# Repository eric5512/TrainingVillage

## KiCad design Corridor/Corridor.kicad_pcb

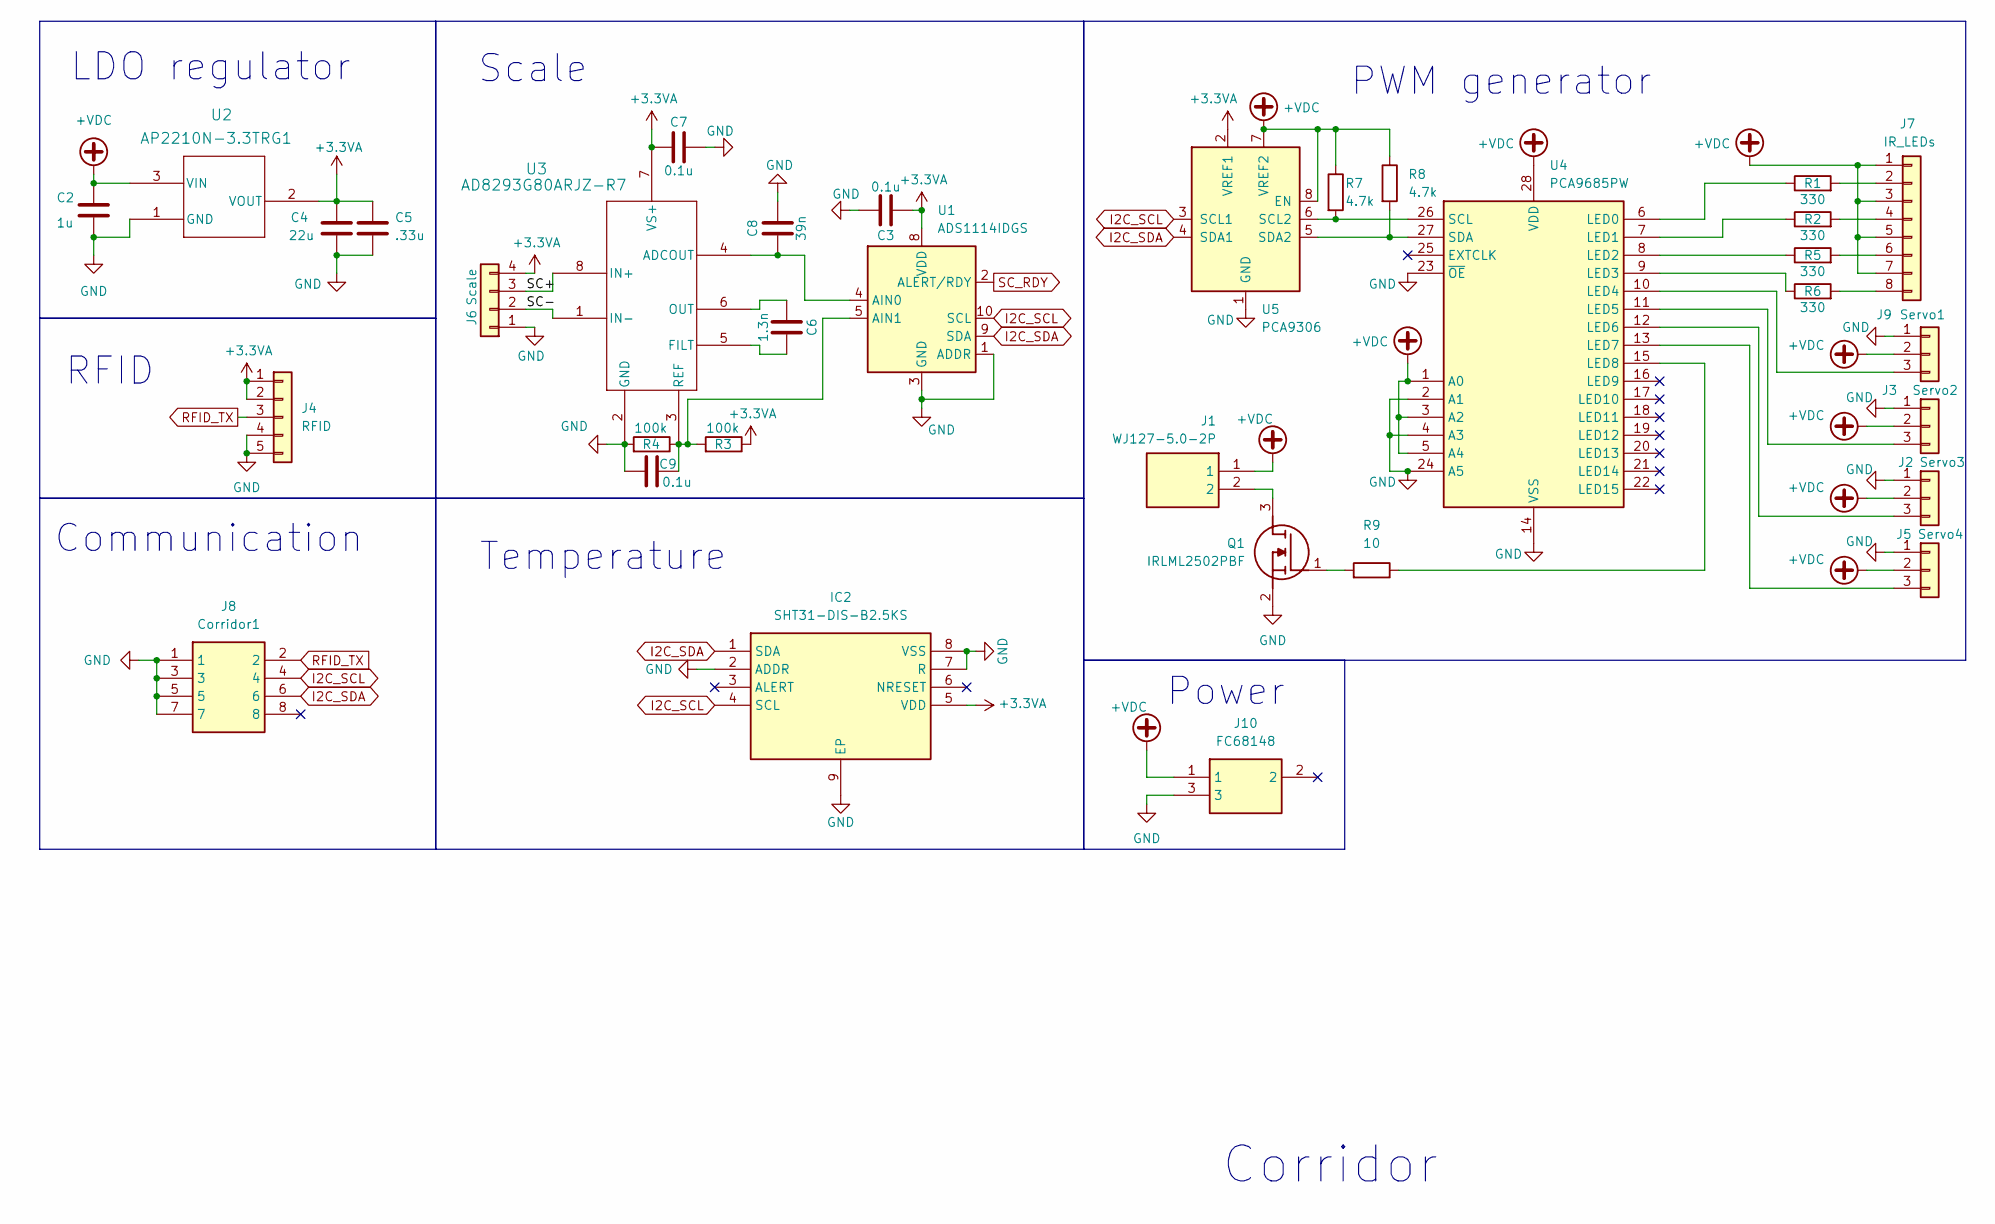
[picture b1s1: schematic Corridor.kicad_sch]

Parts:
C2: 1u; C_1206_3216Metric_Pad1.33x1.80mm_HandSolder
C3, C7, C9: 0.1u; C_1206_3216Metric_Pad1.33x1.80mm_HandSolder
C4: 22u; C_Elec_5x5.8
C5: .33u; C_1206_3216Metric_Pad1.33x1.80mm_HandSolder
C6: 1.3n; C_1206_3216Metric_Pad1.33x1.80mm_HandSolder
C8: 39n; C_1206_3216Metric_Pad1.33x1.80mm_HandSolder
IC2: SHT31-DIS-B2.5KS; SON50P250X250X100-9N-D; Manufacturer_Part_Number SHT31-DIS-B2.5KS; Mouser Part Number 403-SHT31-DIS-B
J1: WJ127-5.0-2P; WJ127502P; Manufacturer_Part_Number WJ127-5.0-2P
J2: Servo3; PinHeader_1x03_P2.54mm_Vertical
J3: Servo2; PinHeader_1x03_P2.54mm_Vertical
J4: RFID; JST_PH_B5B-PH-K_1x05_P2.00mm_Vertical
J5: Servo4; PinHeader_1x03_P2.54mm_Vertical
J6: Scale; JL308-25404G01
J7: IR_LEDs; JL500_8
J8: Corridor1; RJ45R08P-A004; Manufacturer_Part_Number RJ45R08P-A004
J9: Servo1; PinHeader_1x03_P2.54mm_Vertical
J10: FC68148; Manufacturer_Part_Number FC68148
Q1: IRLML2502PBF; SOT95P237X112-3N; Manufacturer_Part_Number IRLML2502PBF; Mouser Part Number N/A
R1, R2, R5, R6: 330; R_1206_3216Metric
R3, R4: 100k; R_1206_3216Metric_Pad1.30x1.75mm_HandSolder
R7, R8: 4.7k; R_0805_2012Metric
R9: 10; R_1206_3216Metric
U1: ADS1114IDGS; DGS10
U2: AP2210N-3.3TRG1; SOT_3.3TRG1_DIO
U3: AD8293G80ARJZ-R7; RJ_8_ADI
U4: PCA9685PW; TSSOP-28_4.4x9.7mm_P0.65mm
U5: PCA9306; VSSOP-8_2.3x2mm_P0.5mm

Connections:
+3.3VA: C3.2, C4.1, C5.1, C7.2, IC2.5 (VDD), J4.1, J4.2, J6.4, R3.1, U1.8 (VDD), U2.2 (VOUT), U3.7 (VS+), U5.2 (VREF1)
+VDC: C2.1, J1.1, J2.2, J3.2, J5.2, J7.1, J7.3, J7.5, J7.7, J9.2, J10.1, R7.1, R8.1, U2.3 (VIN), U4.1 (A0), U4.3 (A2), U4.5 (A4), U4.28 (VDD), U5.7 (VREF2), U5.8 (EN)
/SC+: J6.3, U3.8 (IN+)
/SC-: J6.2, U3.1 (IN-)
GND: C2.2, C3.1, C4.2, C5.2, C7.1, C8.1, C9.2, IC2.2 (ADDR), IC2.7 (R), IC2.8 (VSS), IC2.9 (EP), J2.1, J3.1, J4.4, J4.5, J5.1, J6.1, J8.1, J8.3, J8.5, J8.7, J9.1, J10.3, Q1.2 (S), R4.2, U1.1 (ADDR), U1.3 (GND), U2.1 (GND), U3.2 (GND), U4.2 (A1), U4.4 (A3), U4.14 (VSS), U4.23 (~OE), U4.24 (A5), U5.1 (GND)
I2C_SCL: IC2.4 (SCL), J8.4, U1.10 (SCL), U5.3 (SCL1)
I2C_SDA: IC2.1 (SDA), J8.6, U1.9 (SDA), U5.4 (SDA1)
unnamed: J2.3, U4.12 (LED6)
unnamed: J3.3, U4.11 (LED5)
unnamed: J5.3, U4.13 (LED7)
unnamed: J7.2, R1.2
unnamed: J7.4, R2.2
unnamed: J7.6, R5.2
unnamed: J7.8, R6.2
unnamed: J9.3, U4.10 (LED4)
unnamed: J1.2, Q1.3 (D)
unnamed: Q1.1 (G), R9.2
unnamed: C8.2, U1.4 (AIN0), U3.4 (ADCOUT)
unnamed: C9.1, R3.2, R4.1, U1.5 (AIN1), U3.3 (REF)
unnamed: C6.1, U3.5 (FILT)
unnamed: C6.2, U3.6 (OUT)
unnamed: R1.1, U4.6 (LED0)
unnamed: R2.1, U4.7 (LED1)
unnamed: R5.1, U4.8 (LED2)
unnamed: R6.1, U4.9 (LED3)
unnamed: R9.1, U4.15 (LED8)
unnamed: R7.2, U4.26 (SCL), U5.6 (SCL2)
unnamed: R8.2, U4.27 (SDA), U5.5 (SDA2)
RFID_TX: J4.3, J8.2
SC_RDY: U1.2 (ALERT/RDY)

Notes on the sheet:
RFID
Scale
Corridor
LDO regulator
Power
Communication
PWM generator
Temperature

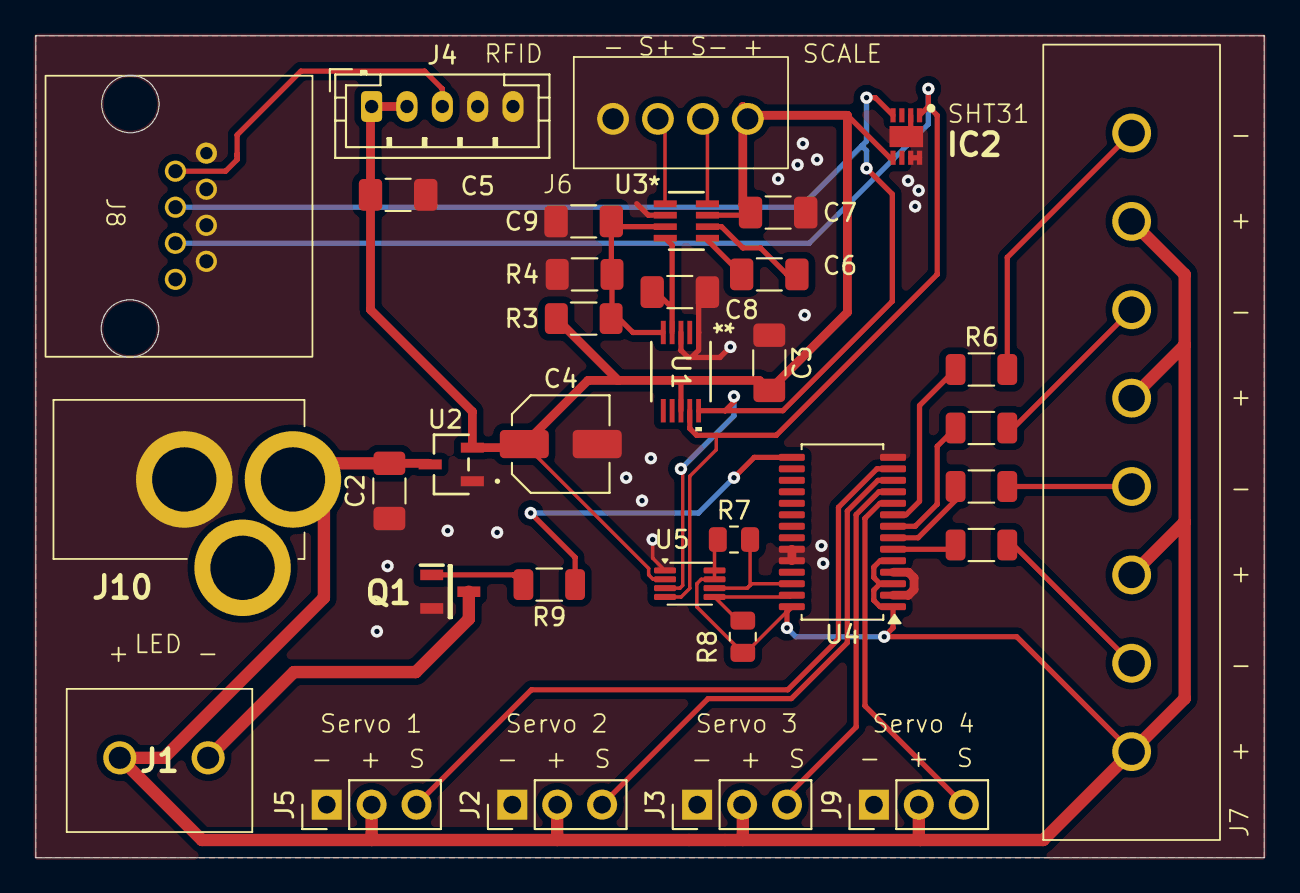
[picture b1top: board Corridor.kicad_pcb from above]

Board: 2 copper layers, 69.5 x 46.5 mm, 34 parts (0 on the bottom side), 29 nets.

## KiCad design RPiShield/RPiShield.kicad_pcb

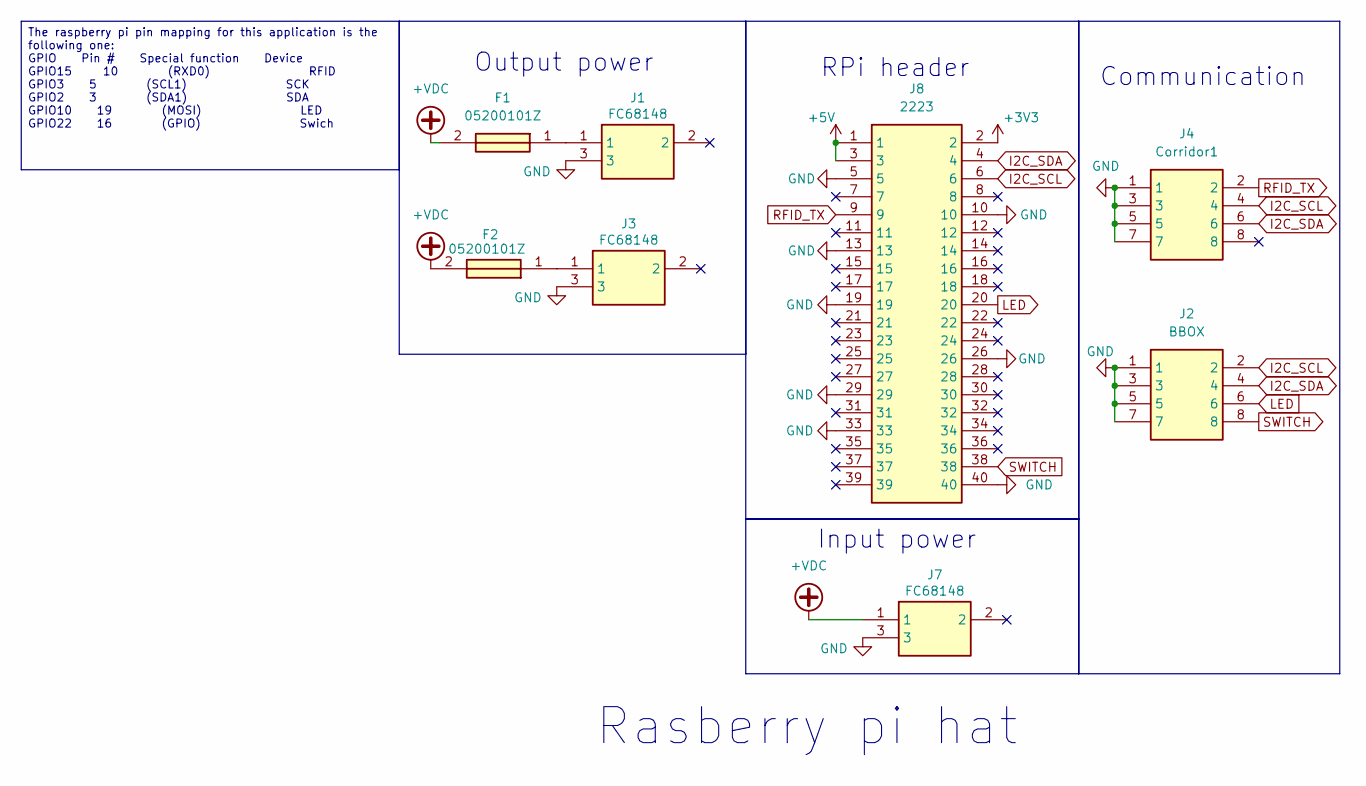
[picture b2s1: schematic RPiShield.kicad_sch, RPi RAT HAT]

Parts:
F1, F2: 05200101Z; Manufacturer_Part_Number 05200101Z; Mouser Part Number 576-05200101Z
J1, J3, J7: FC68148; Manufacturer_Part_Number FC68148
J2: BBOX; RJ45R08P-A004; Manufacturer_Part_Number RJE031880416
J4: Corridor1; RJ45R08P-A004; Manufacturer_Part_Number RJE031880416
J8: 2223; RHDR40W64P254X254_2X20_5105X500X865P; Manufacturer_Part_Number 2223

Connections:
+3V3: J8.2
+5V: J8.1, J8.3
+VDC: F1.2, F2.2, J7.1
GND: J1.3, J2.1, J2.3, J2.5, J2.7, J3.3, J4.1, J4.3, J4.5, J4.7, J7.3, J8.5, J8.10, J8.13, J8.19, J8.26, J8.29, J8.33, J8.40
I2C_SCL: J2.2, J4.4, J8.6
I2C_SDA: J2.4, J4.6, J8.4
LED: J2.6, J8.20
unnamed: F1.1, J1.1
unnamed: F2.1, J3.1
RFID_TX: J4.2, J8.9
SWITCH: J2.8, J8.38

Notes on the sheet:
Input power
Communication
Rasberry pi hat
RPi header
Output power
The raspberry pi pin mapping for this application is the following one: GPIO Pin # Special function Device GPIO15 10 (RXD0) RFID GPIO3 5 (SCL1) SCK GPIO2 3 (SDA1) SDA GPIO10 19 (MOSI) LED GPIO22 16 (GPIO) Swich

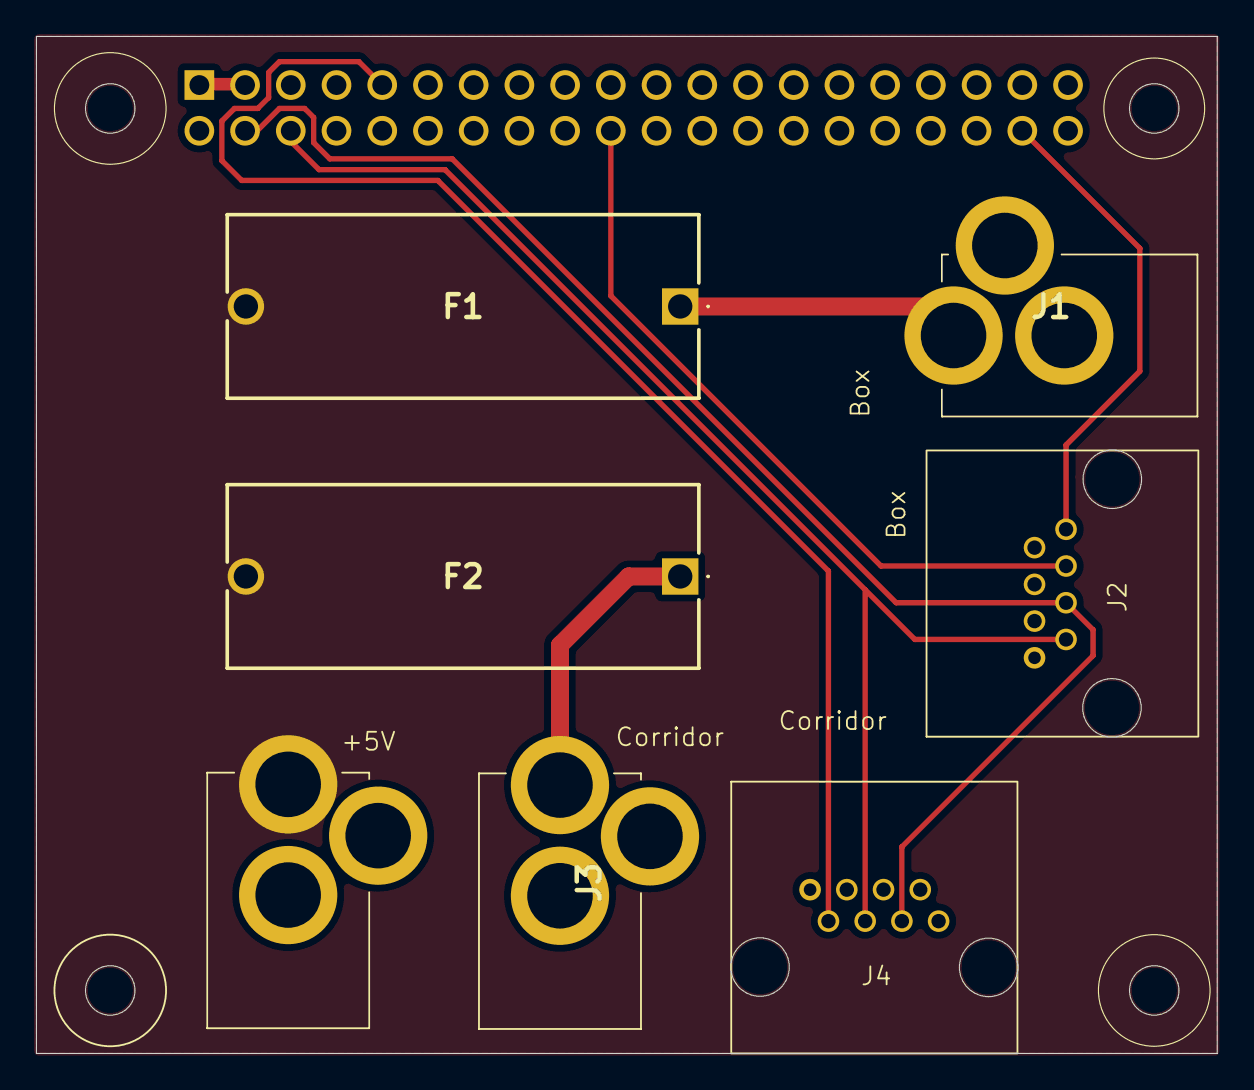
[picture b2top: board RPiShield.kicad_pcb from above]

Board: 2 copper layers, 65.6 x 56.5 mm, 8 parts (1 on the bottom side), 10 nets.

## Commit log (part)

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2026-03-18 Creating repo for training village circuits
2026-03-20 Adding fuseholder to the HAT
2026-04-10 New TrainingVillage version
